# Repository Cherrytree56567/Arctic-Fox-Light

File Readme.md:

# Minecraft Arctic Fox Lamp
A simple Minecraft Themed Arctic Fox Lamp that features an ESP32 C6 Mini with ESP Matter Support which supports Temperature, Hue/Sat and Brightness.

## Features
 - Custom Color LED
 - Smart Home Integration
 - Matter Support
 - Enclosure

## Build
To Run the Matter ESP32 Program, install `ESP-IDF`:
```
git clone --recursive https://github.com/espressif/esp-idf.git
cd esp-idf
git submodule update --init --recursive
./install.sh
cd ../
```
Install `ESP-Matter`:
```
git clone https://github.com/espressif/esp-matter.git
cd esp-matter
git submodule update
cd connectedhomeip/connedtedhomeip/
git submodule update
cd ../../
```
Next source both repo's:
```
cd esp-idf
source ./export.sh
cd ../
cd esp-matter
source ./export.sh
cd ../
```

Then build the project by running
```
idf.py build
```

## Running
To run the application, run:
```
idf.py flash
```

## Credits
 - [Template ESP32 Matter Repo](https://github.com/oidebrett/starter-esp-matter-app)

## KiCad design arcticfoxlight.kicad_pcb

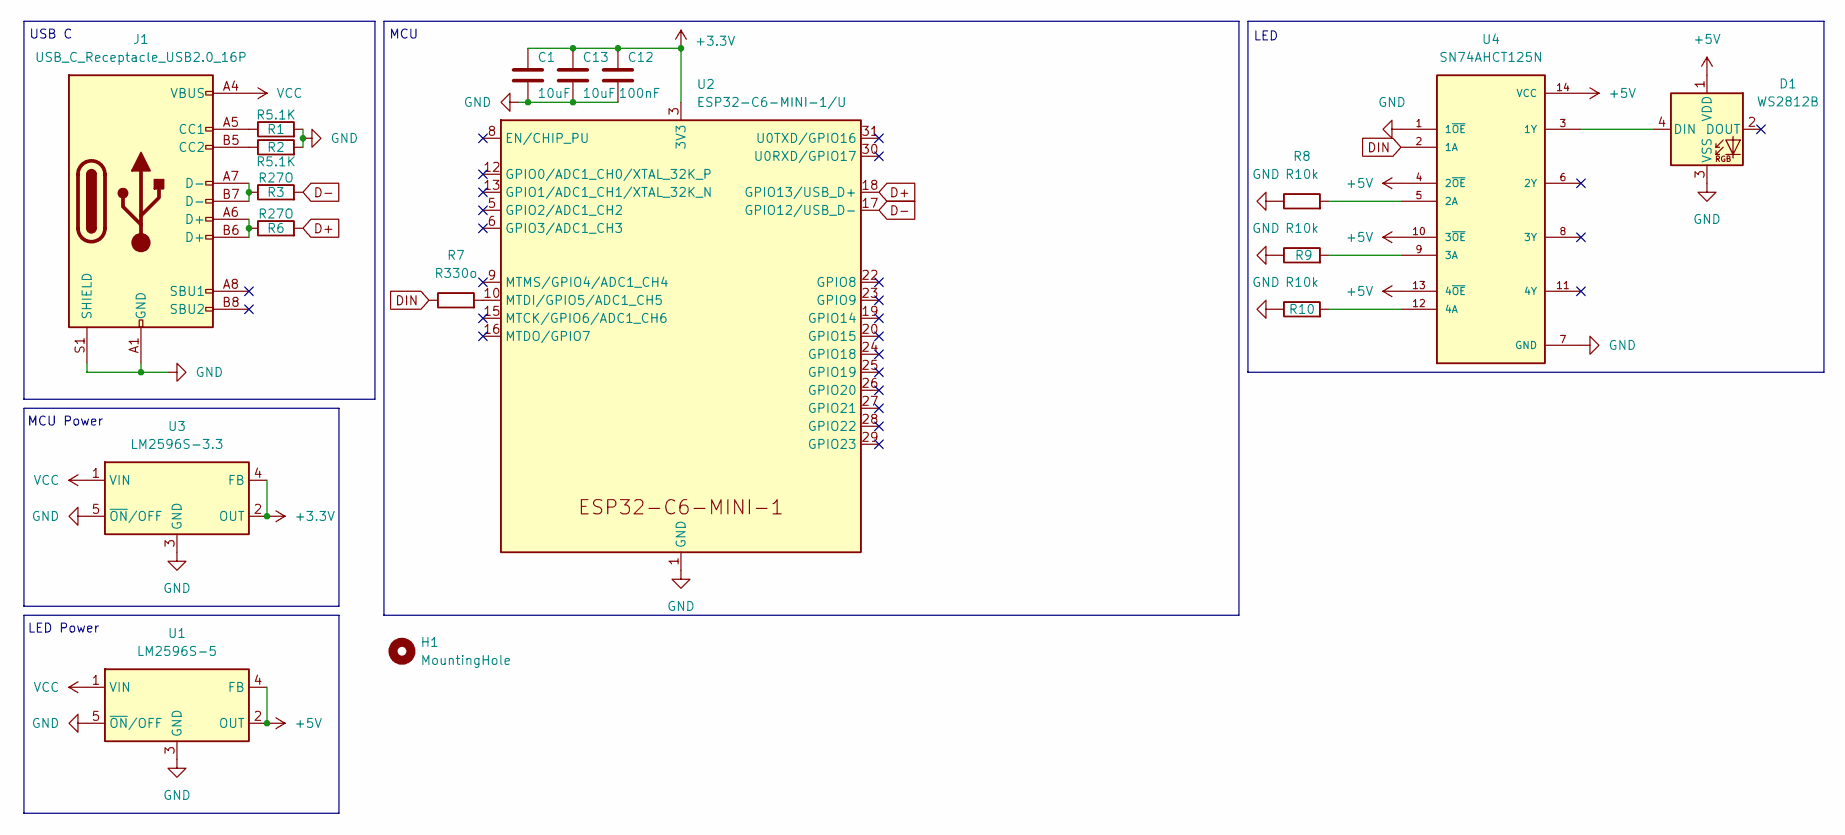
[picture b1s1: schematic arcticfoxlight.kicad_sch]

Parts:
C1, C13: 10uF; C_0805_2012Metric_Pad1.18x1.45mm_HandSolder; LCSC C15850
C12: 100nF; C_0805_2012Metric_Pad1.18x1.45mm_HandSolder; LCSC C49678
D1: WS2812B; LED_WS2812B_PLCC4_5.0x5.0mm_P3.2mm
H1: MountingHole; MountingHole_2.2mm_M2
J1: USB_C_Receptacle_USB2.0_16P; USB_C_Receptacle_HCTL_HC-TYPE-C-16P-01A
R1, R2: R5.1K; R_0201_0603Metric_Pad0.64x0.40mm_HandSolder
R3, R6: R27O; R_0201_0603Metric_Pad0.64x0.40mm_HandSolder
R7: R330o; R_0201_0603Metric_Pad0.64x0.40mm_HandSolder
R8, R9, R10: R10k; R_0201_0603Metric_Pad0.64x0.40mm_HandSolder
U1: LM2596S-5; TO-263-5_TabPin3
U2: ESP32-C6-MINI-1/U; ESP32-C6-MINI-1
U3: LM2596S-3.3; TO-263-5_TabPin3
U4: SN74AHCT125N; DIP794W45P254L1930H508Q14; PARTREV Q

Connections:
+3.3V: C1.1, C12.1, C13.1, U2.3 (3V3), U3.2 (OUT), U3.4 (FB)
+5V: D1.1 (VDD), U1.2 (OUT), U1.4 (FB), U4.4 (2~OE), U4.10 (3~OE), U4.13 (4~OE), U4.14 (VCC)
D+: R6.2, U2.18 (GPIO13/USB_D+)
D-: R3.2, U2.17 (GPIO12/USB_D-)
DIN: R7.1, U4.2 (1A)
GND: C1.2, C12.2, C13.2, D1.3 (VSS), J1.A1 (GND), J1.A12 (GND), J1.B1 (GND), J1.B12 (GND), J1.S1 (SHIELD), R1.2, R2.2, R8.1, R9.1, R10.1, U1.3 (GND), U1.5 (~ON/OFF), U2.1 (GND), U2.2 (GND), U2.11 (GND), U2.14 (GND), U2.36 (GND), U2.37 (GND), U2.38 (GND), U2.39 (GND), U2.40 (GND), U2.41 (GND), U2.42 (GND), U2.43 (GND), U2.44 (GND), U2.45 (GND), U2.46 (GND), U2.47 (GND), U2.48 (GND), U2.49 (GND), U2.50 (GND), U2.51 (GND), U2.52 (GND), U2.53 (GND), U3.3 (GND), U3.5 (~ON/OFF), U4.1 (1~OE), U4.7 (GND)
unnamed: D1.4 (DIN), U4.3 (1Y)
unnamed: J1.A5 (CC1), R1.1
unnamed: J1.B5 (CC2), R2.1
unnamed: J1.A6 (D+), J1.B6 (D+), R6.1
unnamed: J1.A7 (D-), J1.B7 (D-), R3.1
unnamed: R7.2, U2.10 (MTDI/GPIO5/ADC1_CH5)
unnamed: R8.2, U4.5 (2A)
unnamed: R9.2, U4.9 (3A)
unnamed: R10.2, U4.12 (4A)
VCC: J1.A4 (VBUS), J1.A9 (VBUS), J1.B4 (VBUS), J1.B9 (VBUS), U1.1 (VIN), U3.1 (VIN)

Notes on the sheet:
LED
USB C
MCU Power
LED Power
MCU

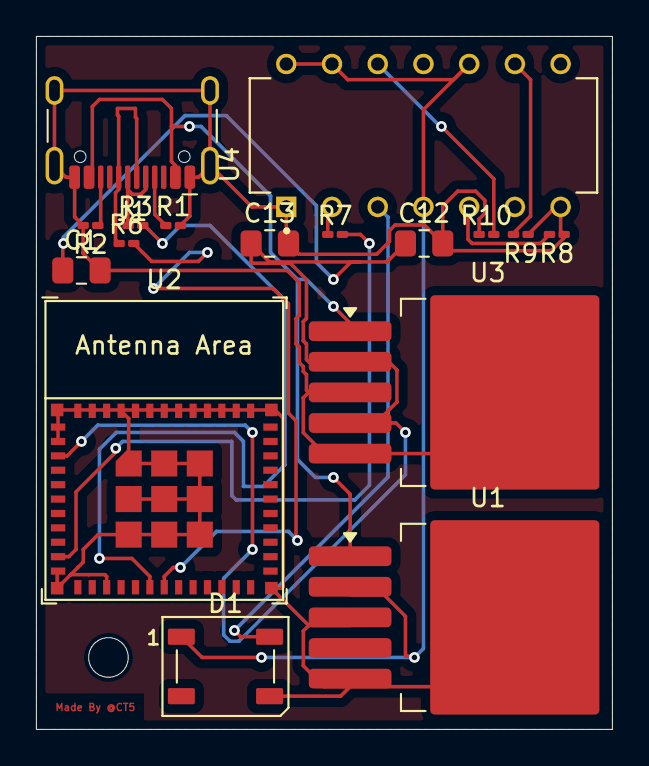
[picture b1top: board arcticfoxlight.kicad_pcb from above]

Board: 2 copper layers, 32.0 x 38.5 mm, 18 parts (0 on the bottom side), 16 nets.

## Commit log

2025-09-17 Day 2
2025-09-17 Day 2.1
2025-09-17 Day 2.2
2025-09-18 Day 4
